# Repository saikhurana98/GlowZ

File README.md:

# Glow-Z 🎵✨

**ESP32-based dual LED strip controller that rocks both RGB and warm white strips!**

## Features

- **Dual Strip Control**: Simultaneous RGB and warm white LED strip control
- **ESP32 Powered**: WiFi connectivity and powerful processing
- **WLED Compatible**: Drop-in compatibility with WLED firmware
- **Compact Design**: Optimized PCB layout for easy integration
- **3D Printable Case**: Custom enclosure design included

## What's Included

### Hardware Files
- **KiCad PCB Design**: Complete schematic and PCB layout files
- **Bill of Materials (BOM)**: Component list with part numbers
- **Assembly Guide**: Step-by-step build instructions

### Enclosure
- **3D Printable Case**: STL files for custom protective enclosure
- **Print Settings**: Recommended settings for optimal results

## Quick Start

1. **Build the PCB** using the provided KiCad files
2. **Flash WLED firmware** to the ESP32
3. **3D print the case** using provided STL files
4. **Connect your LED strips** and power up
5. **Configure via WLED web interface**

## Specifications

- **Input Voltage**: 5-24V DC
- **LED Strip Types**: RGB (WS2812B/SK6812) + Warm White strips
- **MCU**: ESP32-WROOM-32
- **Connectivity**: WiFi 802.11 b/g/n
- **Control**: WLED web interface, mobile app, or API

## Getting Started

### Prerequisites
- KiCad 7.x or newer
- 3D printer (for case)
- Basic soldering skills

### Building
1. Open the KiCad project files
2. Generate Gerber files for PCB manufacturing
3. Order components from the BOM
4. Solder components following the assembly guide
5. Flash WLED firmware

## Contributing

Found a bug or have an improvement? Feel free to open an issue or submit a pull request!

## License

This project is open source. See LICENSE file for details.

---

*"Because your LEDs deserve to drop the hottest beats!"* 🎛️

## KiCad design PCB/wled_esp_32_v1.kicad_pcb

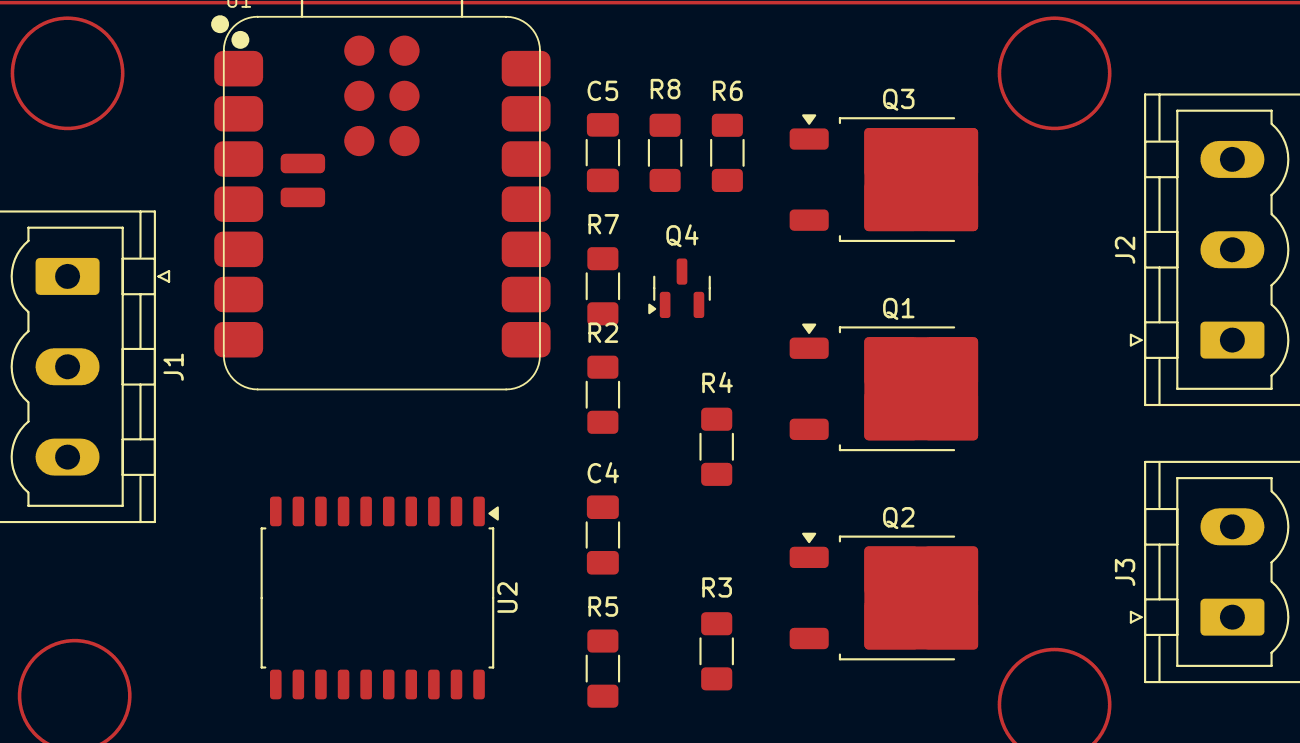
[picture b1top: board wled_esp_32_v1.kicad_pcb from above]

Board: 2 copper layers, 18 parts (0 on the bottom side), 15 nets, no tracks yet.

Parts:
C4, C5: 0.1uf; C_1206_3216Metric_Pad1.33x1.80mm_HandSolder
J1: PWR IN; PhoenixContact_MSTBVA_2,5_3-G-5,08_1x03_P5.08mm_Vertical
J2: Neopixel_1; PhoenixContact_MSTBVA_2,5_3-G-5,08_1x03_P5.08mm_Vertical
J3: PWM_STRIP_1; PhoenixContact_MSTBVA_2,5_2-G-5,08_1x02_P5.08mm_Vertical
Q1, Q2: IRFR024N; TO-252-2
Q3: IRFR5305; TO-252-2
Q4: MMBT2222A; SOT-23
R2, R7: 470 OHM; R_1206_3216Metric_Pad1.30x1.75mm_HandSolder
R3, R4, R5, R6: 10K OHM; R_1206_3216Metric_Pad1.30x1.75mm_HandSolder
R8: 1K OHM; R_1206_3216Metric_Pad1.30x1.75mm_HandSolder
U1: XIAO-ESP32-C3-SMD; XIAO-ESP32C3-SMD
U2: 74AHCT244; Infineon_SOIC-20W_7.6x12.8mm_P1.27mm

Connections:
+5V: C4.2, C5.1, J1.2, Q3.2 (D), R5.1, R6.2, U1.14 (5V), U2.20 (VCC)
+12V: J1.3, J3.1
GND: C4.1, J1.1, J2.3, Q1.3 (S), Q2.3 (S), Q4.2 (E), R3.1, R4.2, U1.16 (GND), U2.1 (1OE), U2.4 (1A1), U2.6 (1A2), U2.8 (1A3), U2.10 (GND), U2.11 (2A3), U2.13 (2A2), U2.15 (2A1), U2.17 (2A0)
NEOPIXEL1_DATA_3V3: U1.3 (GPIO4_A2_D2), U2.2 (1A0)
NEOPIXEL1_DATA_5V: J2.2, U2.18 (1Y0)
NEOPIXEL1_PWR_DPIN_3V3: R7.2, U1.2 (GPIO3_A1_D1)
NEOPIXEL1_PWR_OUT: J2.1, Q3.3 (S)
unnamed: C5.2, U1.13 (GND)
unnamed: Q1.1 (G), Q2.1 (G), R2.1, R3.2, R4.1
unnamed: Q3.1 (G), R6.1, R8.1
unnamed: Q4.1 (B), R7.1
unnamed: Q4.3 (C), R8.2
unnamed: R5.2, U2.19 (2OE)
PWM1_DATA: R2.2, U1.11 (GPIO10_D10_MOSI)
PWM_LED_OUT: J3.2, Q1.2 (D), Q2.2 (D)

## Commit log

2025-06-27 update readme.md with basic info
2025-06-28 add initial schematic
2025-07-02 checkpoint pcb files
